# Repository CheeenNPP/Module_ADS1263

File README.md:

# Module_ADS1263
TI ADS1263 32bit ADC module.

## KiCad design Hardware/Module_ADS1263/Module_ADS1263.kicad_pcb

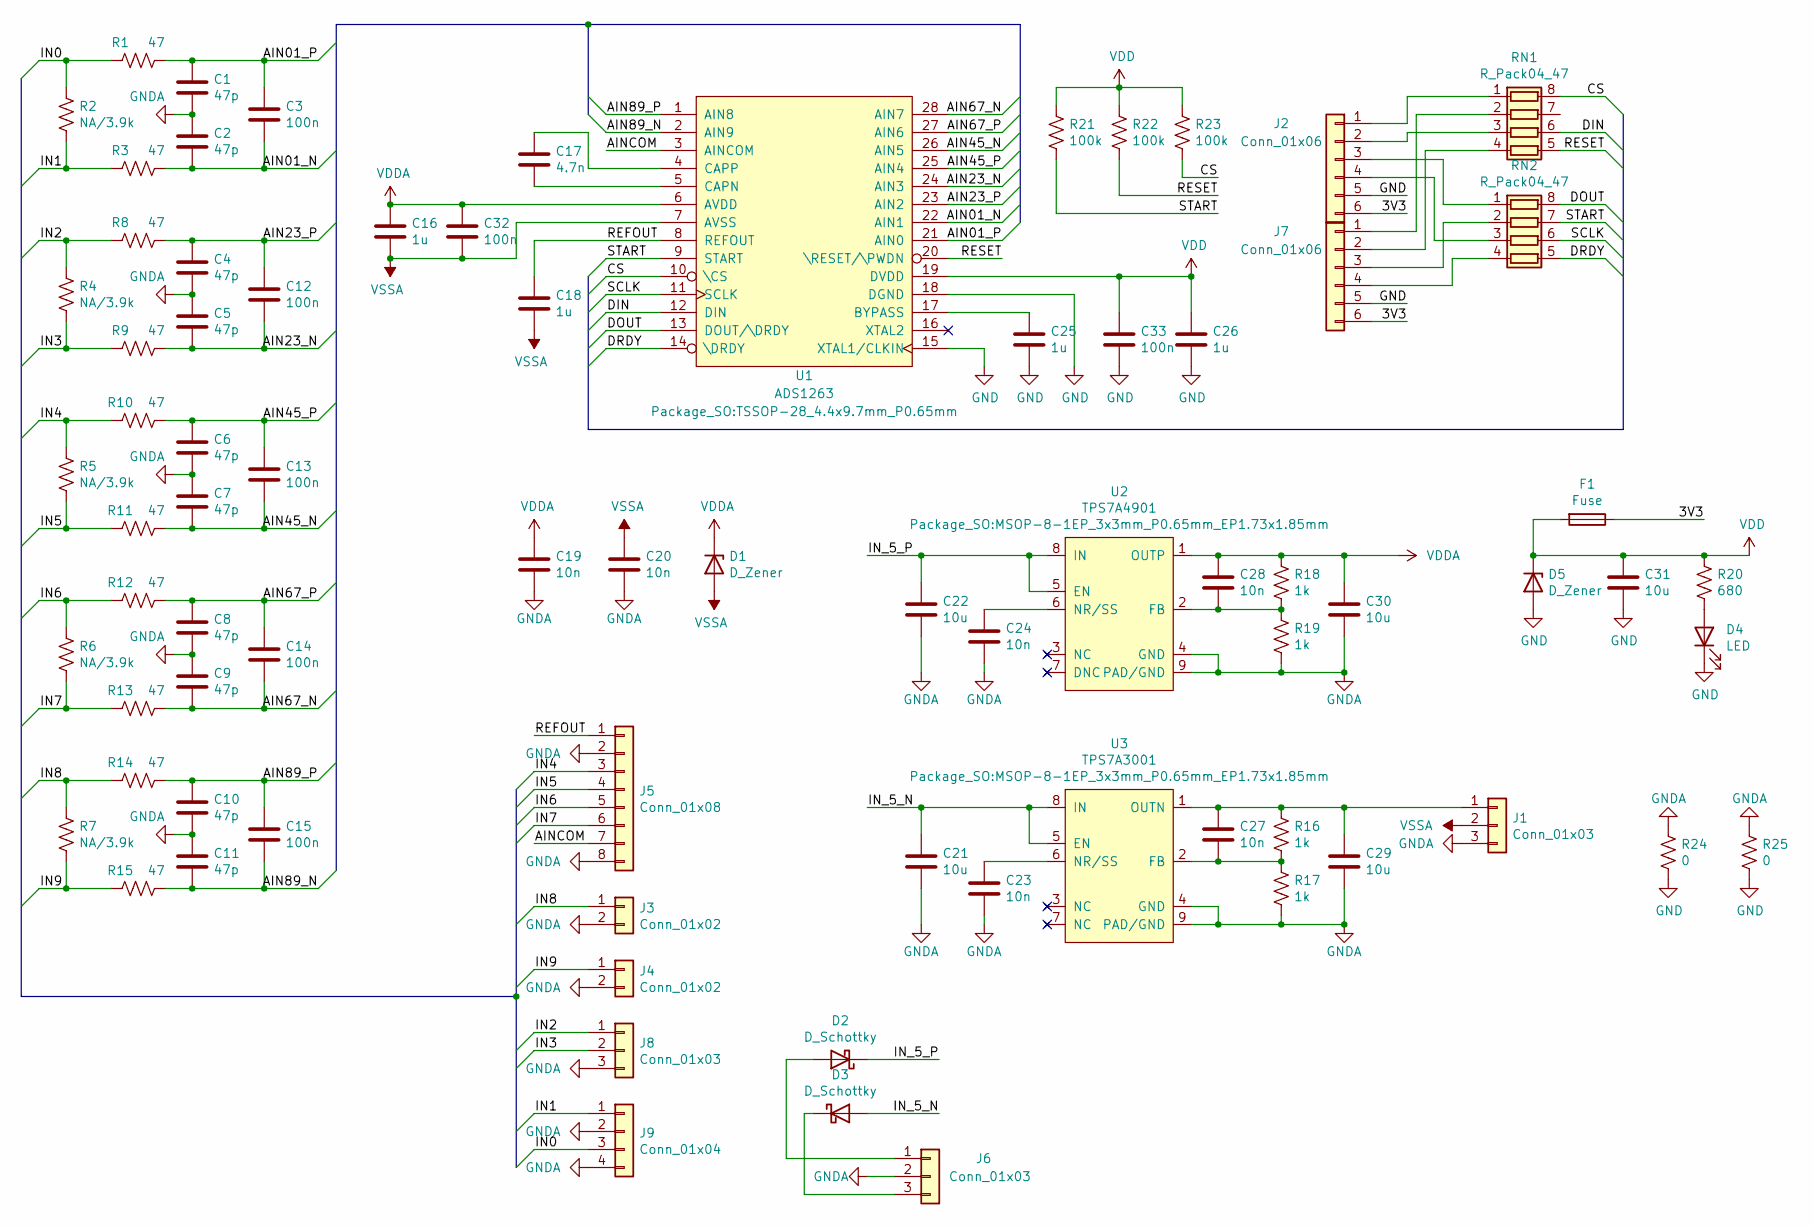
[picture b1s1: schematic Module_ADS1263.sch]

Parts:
C1, C2, C4, C5, C6, C7, C8, C9, C10, C11: 47p; C_0402_1005Metric
C3, C12, C13, C14, C15, C32, C33: 100n; C_0603_1608Metric
C16, C18, C25, C26: 1u; C_0603_1608Metric
C17: 4.7n; C_0402_1005Metric
C19, C20, C23, C24, C27, C28: 10n; C_0402_1005Metric
C21, C22, C29, C30, C31: 10u; C_1206_3216Metric
D1, D5: D_Zener; D_SOD-123
D2, D3: D_Schottky; D_SOD-123
D4: LED; LED_0805_2012Metric
F1: Fuse; Fuse_0805_2012Metric
J1: Conn_01x03; PinHeader_1x03_P2.54mm_Vertical
J2, J7: Conn_01x06; PinHeader_1x06_P2.54mm_Vertical
J3, J4: Conn_01x02; SMA_Samtec_SMA-J-P-X-ST-EM1_EdgeMount
J5: Conn_01x08; PhoenixContact_MC_1,5_8-G-3.81_1x08_P3.81mm_Horizontal
J6: Conn_01x03; PhoenixContact_MC_1,5_3-G-3.81_1x03_P3.81mm_Horizontal
J8: Conn_01x03; JST_XH_S3B-XH-A-1_1x03_P2.50mm_Horizontal
J9: Conn_01x04; PinHeader_2x02_P2.54mm_Horizontal
R1, R3, R8, R9, R10, R11, R12, R13, R14, R15: 47; R_0402_1005Metric
R2, R4, R5, R6, R7: NA/3.9k; R_0402_1005Metric
R16, R17, R18, R19: 1k; R_0402_1005Metric
R20: 680; R_0805_2012Metric
R21, R22, R23: 100k; R_0402_1005Metric
R24, R25: 0; R_1206_3216Metric
RN1, RN2: R_Pack04_47; R_Array_Convex_4x0603
U1: ADS1263; TSSOP-28_4.4x9.7mm_P0.65mm
U2: TPS7A4901; MSOP-8-1EP_3x3mm_P0.65mm_EP1.73x1.85mm
U3: TPS7A3001; MSOP-8-1EP_3x3mm_P0.65mm_EP1.73x1.85mm

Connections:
/3V3: F1.1, J2.6, J7.6
/AIN01_N: C2.2, C3.2, R3.1, U1.22 (AIN1)
/AIN01_P: C1.1, C3.1, R1.1, U1.21 (AIN0)
/AIN23_N: C5.2, C12.2, R9.1, U1.24 (AIN3)
/AIN23_P: C4.1, C12.1, R8.1, U1.23 (AIN2)
/AIN45_N: C7.2, C13.2, R11.1, U1.26 (AIN5)
/AIN45_P: C6.1, C13.1, R10.1, U1.25 (AIN4)
/AIN67_N: C9.2, C14.2, R13.1, U1.28 (AIN7)
/AIN67_P: C8.1, C14.1, R12.1, U1.27 (AIN6)
/AIN89_N: C11.2, C15.2, R15.1, U1.2 (AIN9)
/AIN89_P: C10.1, C15.1, R14.1, U1.1 (AIN8)
/AINCOM: J5.7, U1.3 (AINCOM)
/CS: R23.1, RN1.8 (R1.2), U1.10 (\CS)
/DIN: RN1.6 (R3.2), U1.12 (DIN)
/DOUT: RN2.8 (R1.2), U1.13 (DOUT/\DRDY)
/DRDY: RN2.5 (R4.2), U1.14 (\DRDY)
/IN0: J9.3, R1.2, R2.2
/IN1: J9.1, R2.1, R3.2
/IN2: J8.1, R4.2, R8.2
/IN3: J8.2, R4.1, R9.2
/IN4: J5.3, R5.2, R10.2
/IN5: J5.4, R5.1, R11.2
/IN6: J5.5, R6.2, R12.2
/IN7: J5.6, R6.1, R13.2
/IN8: J3.1, R7.2, R14.2
/IN9: J4.1, R7.1, R15.2
/IN_5_N: C21.1, D3.2 (A), U3.5 (EN), U3.8 (IN)
/IN_5_P: C22.1, D2.1 (K), U2.5 (EN), U2.8 (IN)
/REFOUT: C18.1, J5.1, U1.8 (REFOUT)
/RESET: R22.1, RN1.5 (R4.2), U1.20 (\RESET/\PWDN)
/SCLK: RN2.6 (R3.2), U1.11 (SCLK)
/START: R21.1, RN2.7 (R2.2), U1.9 (START)
GND: C25.2, C26.2, C31.2, C33.2, D4.1 (K), D5.2 (A), J2.5, J7.5, R24.2, R25.2, U1.15 (XTAL1/CLKIN), U1.18 (DGND)
GNDA: C1.2, C2.1, C4.2, C5.1, C6.2, C7.1, C8.2, C9.1, C10.2, C11.1, C19.2, C20.2, C21.2, C22.2, C23.2, C24.2, C29.2, C30.2, J1.3, J3.2, J4.2, J5.2, J5.8, J6.2, J8.3, J9.2, J9.4, R17.1, R19.1, R24.1, R25.1, U2.4 (GND), U2.9 (PAD/GND), U3.4 (GND), U3.9 (PAD/GND)
unnamed: C17.1, U1.4 (CAPP)
unnamed: C17.2, U1.5 (CAPN)
unnamed: C23.1, U3.6 (NR/SS)
unnamed: C24.1, U2.6 (NR/SS)
unnamed: C25.1, U1.17 (BYPASS)
unnamed: C27.1, C29.1, J1.1, R16.2, U3.1 (OUTN)
unnamed: C27.2, R16.1, R17.2, U3.2 (FB)
unnamed: C28.2, R18.1, R19.2, U2.2 (FB)
unnamed: D2.2 (A), J6.1
unnamed: D3.1 (K), J6.3
unnamed: D4.2 (A), R20.2
unnamed: J2.1, RN1.1 (R1.1)
unnamed: J2.2, RN1.3 (R3.1)
unnamed: J2.3, RN2.1 (R1.1)
unnamed: J2.4, RN2.3 (R3.1)
unnamed: J7.1, RN1.2 (R2.1)
unnamed: J7.2, RN1.4 (R4.1)
unnamed: J7.3, RN2.2 (R2.1)
unnamed: J7.4, RN2.4 (R4.1)
VDD: C26.1, C31.1, C33.1, D5.1 (K), F1.2, R20.1, R21.2, R22.2, R23.2, U1.19 (DVDD)
VDDA: C16.1, C19.1, C28.1, C30.1, C32.1, D1.1 (K), R18.2, U1.6 (AVDD), U2.1 (OUTP)
VSSA: C16.2, C18.2, C20.1, C32.2, D1.2 (A), J1.2, U1.7 (AVSS)

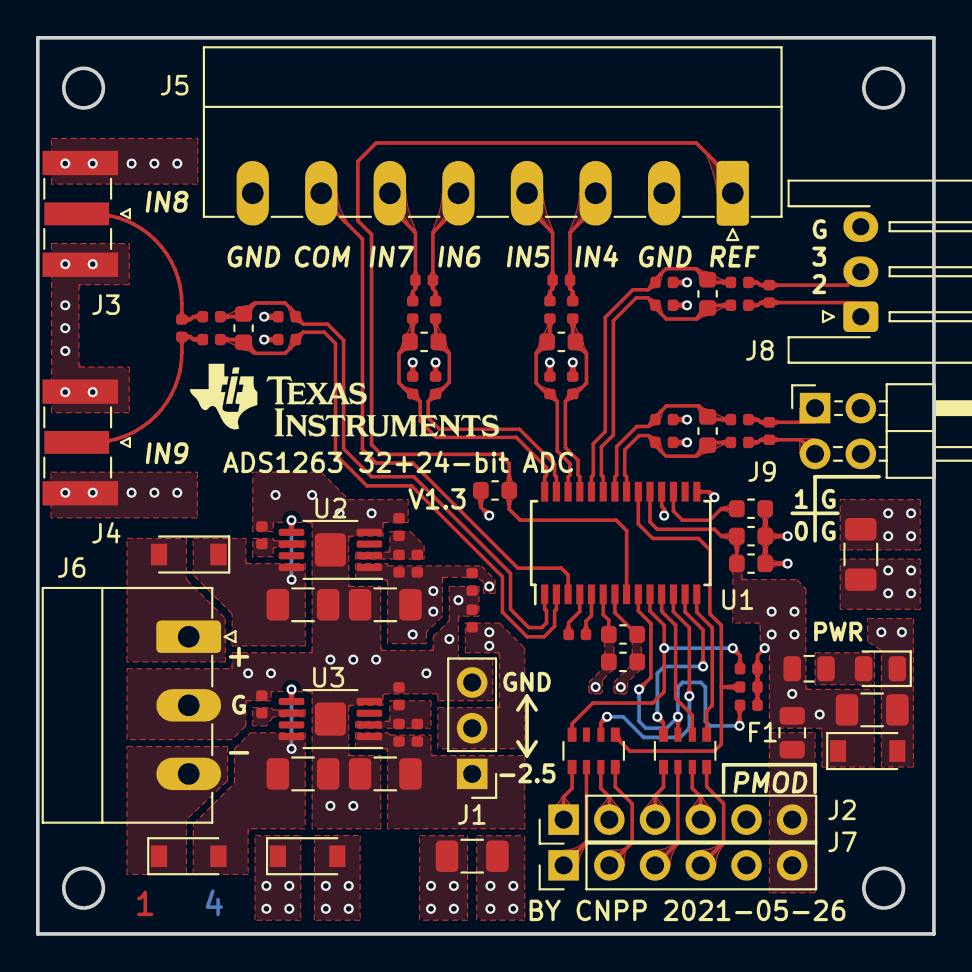
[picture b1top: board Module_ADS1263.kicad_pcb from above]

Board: 4 copper layers, 49.8 x 49.8 mm, 78 parts (0 on the bottom side), 56 nets.

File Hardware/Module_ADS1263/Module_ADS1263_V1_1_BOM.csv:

"ID";"指示器";"包";"数量";"名称";"供应商和参考";
1;"REF**";"KiCad-Logo2_5mm_SilkScreen";1;"KiCad-Logo2_5mm_SilkScreen";;;
2;"G***";"TI_0";1;"LOGO";;;
3;"R25,R24";"R_1206_3216Metric";2;"0";;;
4;"J9";"PinHeader_2x02_P2.54mm_Horizontal";1;"Conn_01x04";;;
5;"J8";"JST_XH_S3B-XH-A-1_1x03_P2.50mm_Horizontal";1;"Conn_01x03";;;
6;"R23,R22,R21";"R_0402_1005Metric";3;"100k";;;
7;"C33,C32,C15,C14,C13,C12,C3";"C_0603_1608Metric";7;"100n";;;
8;"F1";"Fuse_0805_2012Metric";1;"Fuse";;;
9;"D5,D1";"D_SOD-123";2;"D_Zener";;;
10;"C31,C30,C29,C22,C21";"C_1206_3216Metric";5;"10u";;;
11;"J4,J3";"SMA_Samtec_SMA-J-P-X-ST-EM1_EdgeMount";2;"Conn_01x02";;;
12;"D3,D2";"D_SOD-123";2;"D_Schottky";;;
13;"R20";"R_0805_2012Metric";1;"680";;;
14;"D4";"LED_0805_2012Metric";1;"LED";;;
15;"RN2,RN1";"R_Array_Convex_4x0603";2;"R_Pack04_47";;;
16;"J7,J2";"PinHeader_1x06_P2.54mm_Vertical";2;"Conn_01x06";;;
17;"J6";"PhoenixContact_MC_1,5_3-G-3.81_1x03_P3.81mm_Horizontal";1;"Conn_01x03";;;
18;"J5";"PhoenixContact_MC_1,5_8-G-3.81_1x08_P3.81mm_Horizontal";1;"Conn_01x08";;;
19;"U2";"MSOP-8-1EP_3x3mm_P0.65mm_EP1.73x1.85mm";1;"TPS7A4901";;;
20;"U3";"MSOP-8-1EP_3x3mm_P0.65mm_EP1.73x1.85mm";1;"TPS7A3001";;;
21;"U1";"TSSOP-28_4.4x9.7mm_P0.65mm";1;"ADS1263";;;
22;"R19,R18,R17,R16";"R_0402_1005Metric";4;"1k";;;
23;"R15,R14,R13,R12,R11,R10,R9,R8,R3,R1";"R_0402_1005Metric";10;"47";;;
24;"R7,R6,R5,R4,R2";"R_0402_1005Metric";5;"NA/3.9k";;;
25;"J1";"PinHeader_1x03_P2.54mm_Vertical";1;"Conn_01x03";;;
26;"C28,C27,C24,C23,C20,C19";"C_0402_1005Metric";6;"10n";;;
27;"C26,C25,C18,C16";"C_0603_1608Metric";4;"1u";;;
28;"C17";"C_0402_1005Metric";1;"4.7n";;;
29;"C11,C10,C9,C8,C7,C6,C5,C4,C2,C1";"C_0402_1005Metric";10;"47p";;;

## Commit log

2021-05-26 First commit.
